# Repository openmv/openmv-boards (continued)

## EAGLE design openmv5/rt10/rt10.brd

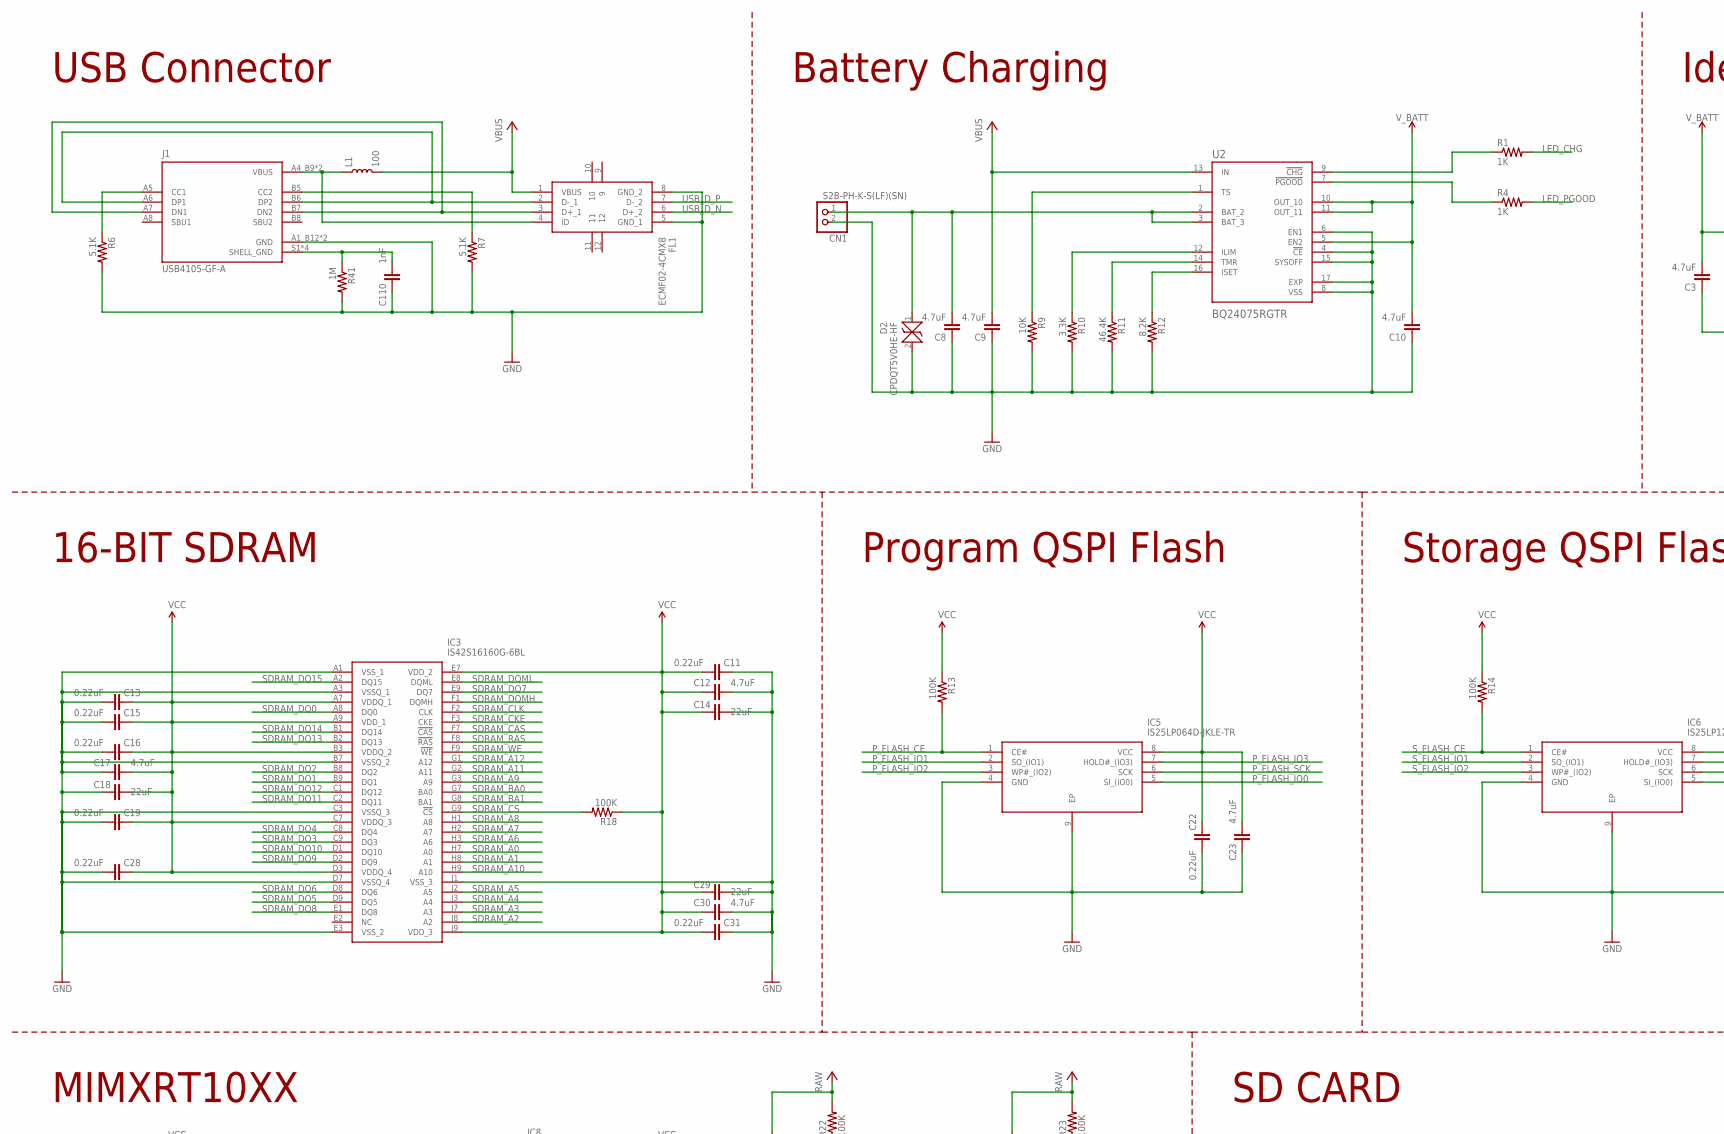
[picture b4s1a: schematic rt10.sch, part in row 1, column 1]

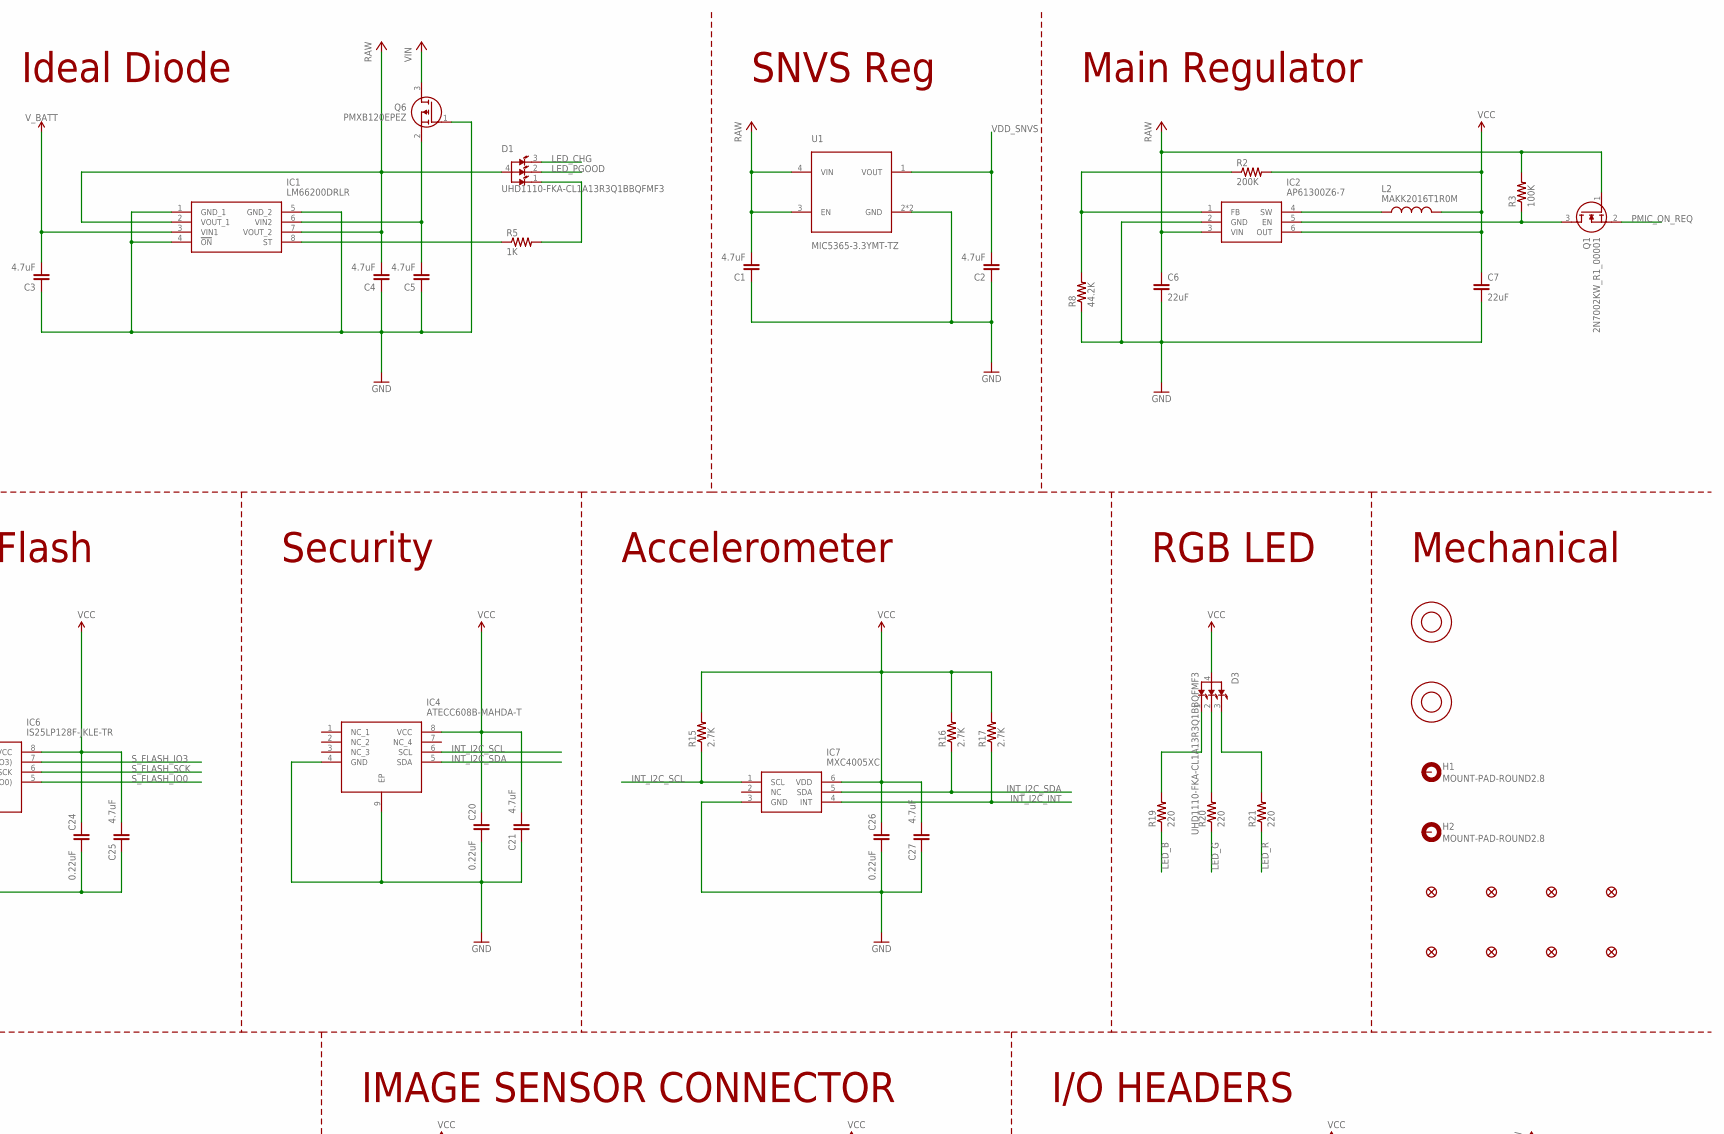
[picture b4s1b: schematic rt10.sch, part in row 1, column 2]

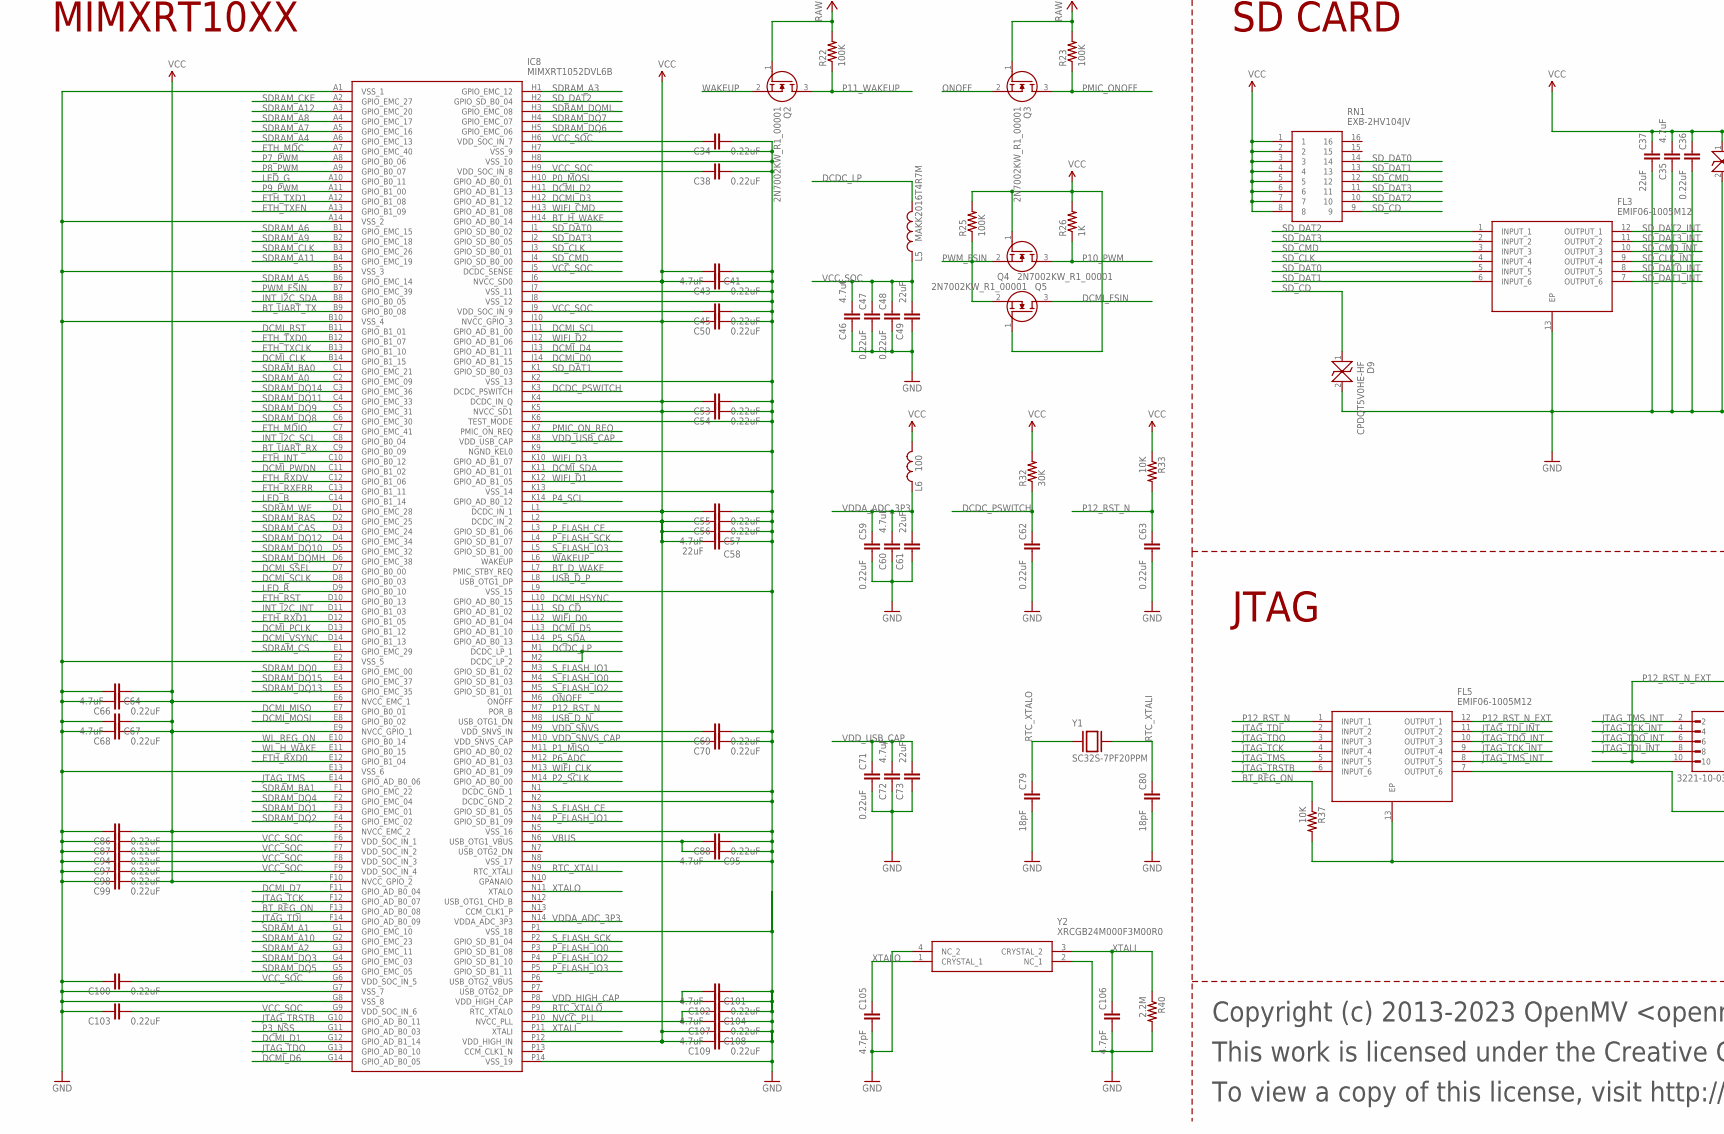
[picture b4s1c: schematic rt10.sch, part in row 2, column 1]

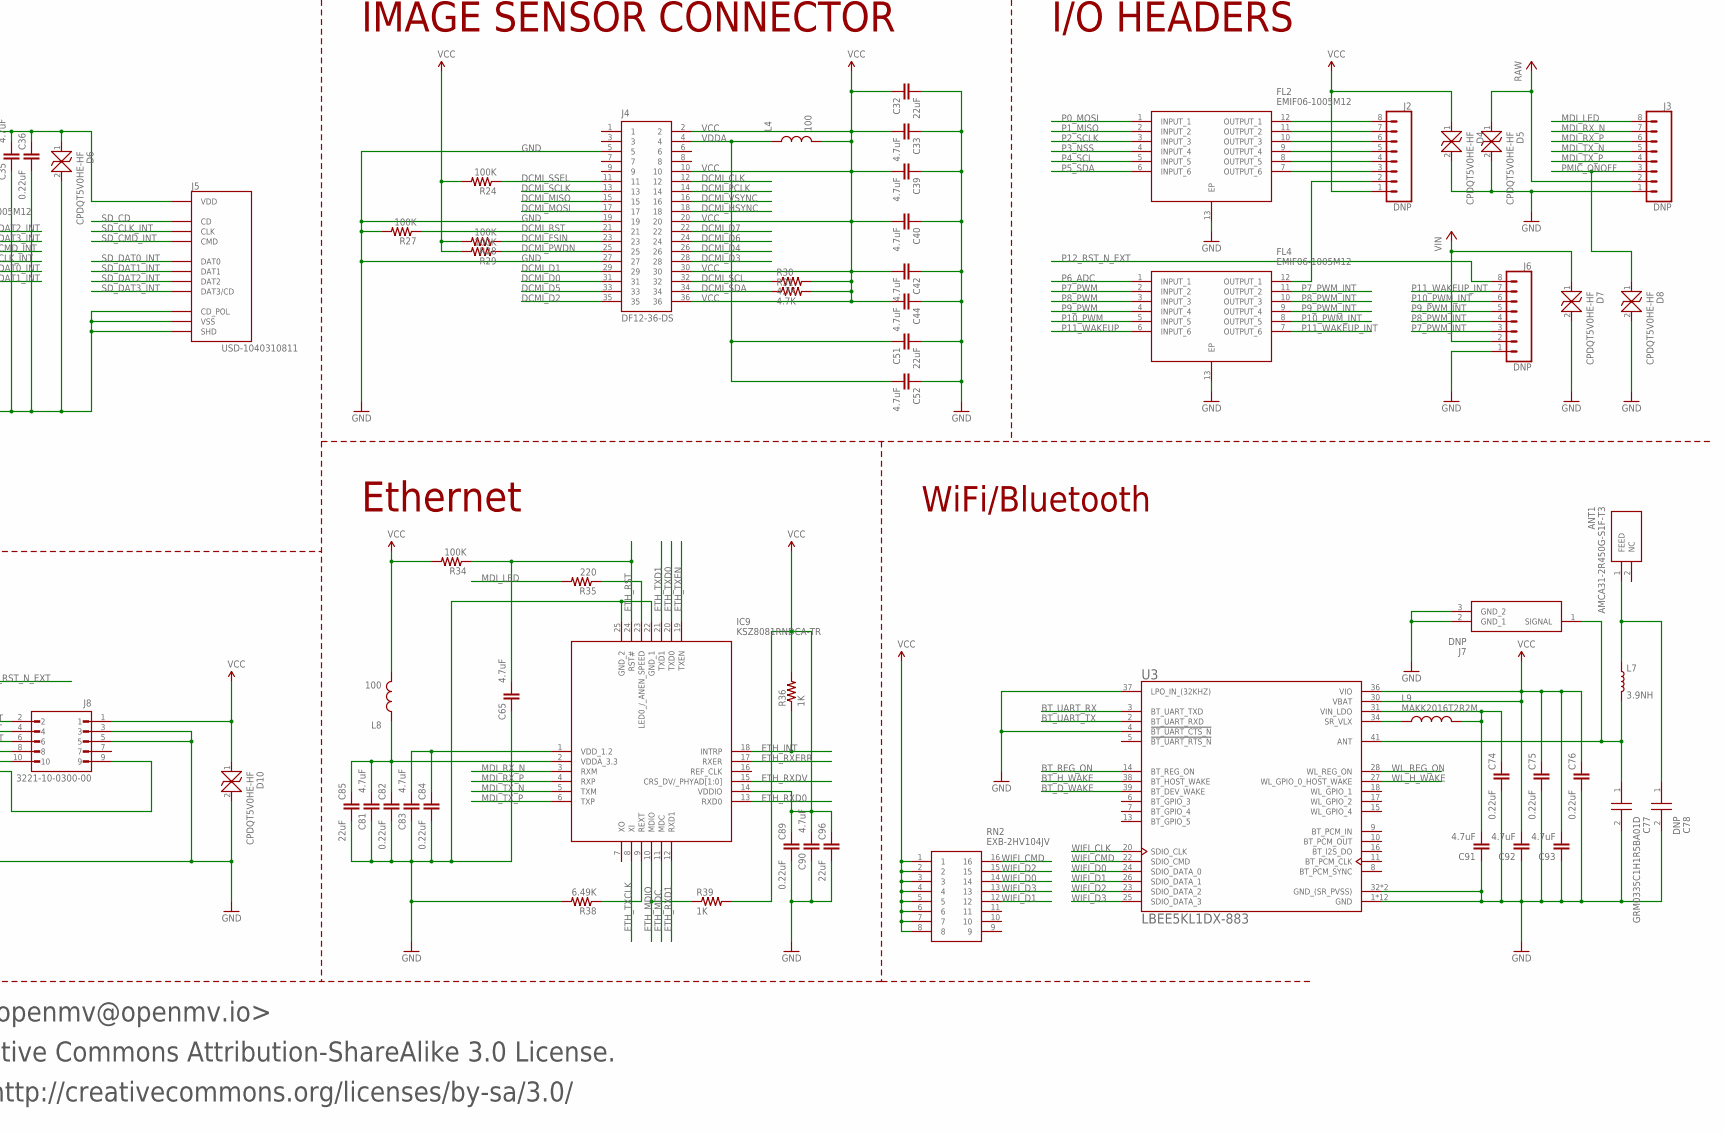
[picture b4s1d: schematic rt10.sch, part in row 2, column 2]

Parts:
ANT1: AMCA31-2R450G-S1F-T3; ANTC3216X140N; MPN AMCA31-2R450G-S1F-T3
C1, C2, C3, C4, C5, C8, C9, C10, C12, C17, C21, C23, C25, C27, C30, C33, C35, C39, C40, C41, C42, C44, C46, C52, C57, C60, C64, C65, C67, C72, C81, C83, C90, C91, C92, C93, C95, C101, C104, C108: 4.7uF; 0402-CAP; MPN JMK105BBJ475MV-F
C6, C7, C14, C18, C29, C32, C37, C49, C51, C58, C61, C73, C85, C96: 22uF; 0805; MPN CL21A226MQQNNNE
C11, C13, C15, C16, C19, C20, C22, C24, C26, C28, C31, C34, C36, C38, C43, C45, C47, C48, C50, C53, C54, C55, C56, C59, C62, C63, C66, C68, C69, C70, C71, C74, C75, C76, C82, C84, C86, C87, C88, C89, C94, C97, C98, C99, C100, C102, C103, C107, C109: 0.22uF; C0201; MPN GRM033R60J224ME15D
C77: GRM0335C1H1R5BA01D; CAPC0603X33N; MPN GRM0335C1H1R5BA01D
C78: DNP; CAPC0603X33N; MPN GRM0335C1H1R5BA01D
C79, C80: 18pF; C0201; MPN GRM0335C1E180JA01D
C105, C106: 4.7pF; C0201; MPN GRM0335C1E4R7CA01D
C110: 1nF; 0402-CAP; MPN VJ0402Y102JXACW1BC
CN1: S2B-PH-K-S(LF)(SN); JST-PH-2-THM-RA; MPN S2B-PH-K-S(LF)(SN)
D1, D3: UHD1110-FKA-CL1A13R3Q1BBQFMF3; LED_UHD1110-FKA-CL1A13R3Q1BBQFMF3; MPN UHD1110-FKA-CL1A13r3q1BBQFMF3
D2, D4, D5, D6, D7, D8, D9, D10: CPDQT5V0HE-HF; CPDQT5V0HEHF; MPN CPDQT5V0HE-HF
FD1, FD2, FD3, FD4, FD5, FD6, FD7, FD8: FIDUCIAL1X2; FIDUCIAL-1X2
FL1: ECMF02-4CMX8; ECMF024CMX8; MPN ECMF02-4CMX8
FL2, FL3, FL4, FL5: EMIF06-1005M12; SON40P150X250X65-13N; MPN EMIF06-1005M12
H1, H2: MOUNT-PAD-ROUND2.8; 2,8-PAD
IC1: LM66200DRLR; SOTFL50P160X60-8N; MPN LM66200DRLR
IC2: AP61300Z6-7; SOTFL50P162X60-6N; MPN AP61300Z6-7
IC3: IS42S16160G-6BL; BGA54C80P9X9_800X800X120; MPN IS42S16160G-6BL
IC4: ATECC608B-MAHDA-T; SON50P300X200X60-9N; MPN ATECC608B-MAHDA-T
IC5: IS25LP064D-JKLE-TR; SON127P500X595X80-9N; MPN IS25LP064D-JKLE-TR
IC6: IS25LP128F-JKLE-TR; SON127P500X595X80-9N; MPN IS25LP128F-JKLE-TR
IC7: MXC4005XC; MPN MXC4005XC
IC8: MIMXRT1052DVL6B; BGA196C65P14X14_1000X1000X143; MPN MIMXRT1052DVL6B
IC9: KSZ8081RNDCA-TR; QFN50P400X400X90-25N; MPN KSZ8081RNDCA-TR
J1: USB4105-GF-A; GCT_USB4105-GF-A; MPN USB4105-GF-A
J2, J3, J6: DNP; 1X08
J4: DF12-36-DS; MPN DF12NB-36DS-0.5V(51)
J5: USD-1040310811; 1040310811; MPN 104031-0811
J7: DNP; 23370191; MPN 2337019-1
J8: 3221-10-0300-00; CNC_3221-10-0300-00; MPN 3221-10-0300-00
L1: 100; 0603; MPN MFBM1V1608-101-R
L2: MAKK2016T1R0M; INDC2016X100N; MPN MAKK2016T1R0M
L4, L6, L8: 100; C0402; MPN MFBM1V1005-101-R
L5: MAKK2016T4R7M; INDC2016X100N; MPN MAKK2016T4R7M
L7: 3.9NH; 0402; MPN L-07C3N9SV6T
L9: MAKK2016T2R2M; INDC2016X100N; MPN MAKK2016T2R2M
M1, M2: 9774030151R; MPN 9774030151R
Q1, Q2, Q3, Q4, Q5: 2N7002KW_R1_00001; SOT65P210X110-3N; MPN 2N7002KW_R1_00001
Q6: PMXB120EPEZ; MPN PMXB120EPEZ
R1, R4, R5, R26, R36, R39: 1K; 0402-RES; MPN CRCW04021K00FKEDC
R2: 200K; 0402-RES; MPN CRCW0402200KFKEDC
R3, R13, R14, R18, R22, R23, R24, R25, R27, R28, R29, R34: 100K; 0402-RES; MPN AC0402FR-07100KL
R6, R7: 5.1K; 0402-RES; MPN RC0402JR-075K1L
R8: 44.2K; 0402-RES; MPN AC0402FR-0744K2L
R9, R33, R37: 10K; 0402-RES; MPN AC0402FR-1310KL
R10: 3.3K; 0402-RES; MPN CRCW04023K30FKEDC
R11: 46.4K; 0402-RES; MPN WR04X4642FTL
R12: 8.2K; 0402-RES; MPN RC0402JR-078K2L
R15, R16, R17: 2.7K; 0402-RES; MPN AC0402JR-072K7L
R19, R20, R21, R35: 220; 0402-RES; MPN CRGCQ0402F220R
R30, R31: 4.7K; 0402-RES; MPN AC0402FR-074K7L
R32: 30K; 0402-RES; MPN 0402WGF3002TCE
R38: 6.49K; 0402-RES; MPN CR0402-FX-6491GLF
R40: 2.2M; 0402-RES; MPN RC0402FR-072M2L
R41: 1M; 0402-RES; MPN CRCW04021M00FKEDC
RN1, RN2: EXB-2HV104JV; EXB2HV104JV
U1: MIC5365-3.3YMT-TZ; VREG_MIC5365-3.3YMT-TZ; MPN MIC5365-3.3YMT-TZ
U2: BQ24075RGTR; QFN50P300X300X100-17N; MPN BQ24075RGTR
U3: LBEE5KL1DX-883; XCVR_LBEE5KL1DX-TEMP; MPN LBEE5KL1DX-883
Y1: SC32S-7PF20PPM; XTAL_ABS07-32.768KHZ-7-T; MPN SC32S-7PF20PPM
Y2: XRCGB24M000F3M00R0; MPN XRCGB24M000F3M00R0

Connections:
ANT: C77.1, J7.1 (SIGNAL), L7.2, U3.41 (ANT)
BAT: C8.2, CN1.1 (2), D2.1, U2.2 (BAT_2), U2.3 (BAT_3)
BT_D_WAKE: IC8.L7 (PMIC_STBY_REQ), U3.39 (BT_DEV_WAKE)
BT_H_WAKE: IC8.H14 (GPIO_AD_B0_14), U3.38 (BT_HOST_WAKE)
BT_REG_ON: IC8.F13 (GPIO_AD_B0_08), R37.1, U3.14 (BT_REG_ON)
BT_UART_RX: IC8.C9 (GPIO_B0_09), U3.3 (BT_UART_TXD)
BT_UART_TX: IC8.B9 (GPIO_B0_08), U3.2 (BT_UART_RXD)
CC1: J1.A5 (CC1), R6.1
CC2: J1.B5 (CC2), R7.1
CHG: R1.1, U2.9 (!CHG)
DCDC_LP: IC8.M1 (DCDC_LP_1), IC8.M2 (DCDC_LP_2), L5.2
DCDC_PSWITCH: C62.1, IC8.K3 (DCDC_PSWITCH), R32.1
DCMI_CLK: IC8.B14 (GPIO_B1_15), J4.12
DCMI_D0: IC8.J14 (GPIO_AD_B1_15), J4.31
DCMI_D1: IC8.G12 (GPIO_AD_B1_14), J4.29
DCMI_D2: IC8.H11 (GPIO_AD_B1_13), J4.35
DCMI_D3: IC8.H12 (GPIO_AD_B1_12), J4.28
DCMI_D4: IC8.J13 (GPIO_AD_B1_11), J4.26
DCMI_D5: IC8.L13 (GPIO_AD_B1_10), J4.33
DCMI_D6: IC8.G14 (GPIO_AD_B0_05), J4.24
DCMI_D7: IC8.F11 (GPIO_AD_B0_04), J4.22
DCMI_FSIN: J4.23, Q5.3 (D), R28.1
DCMI_HSYNC: IC8.L10 (GPIO_AD_B0_15), J4.18
DCMI_MISO: IC8.E7 (GPIO_B0_01), J4.15
DCMI_MOSI: IC8.E8 (GPIO_B0_02), J4.17
DCMI_PCLK: IC8.D13 (GPIO_B1_12), J4.14
DCMI_PWDN: IC8.C11 (GPIO_B1_02), J4.25, R29.1
DCMI_RST: IC8.B11 (GPIO_B1_01), J4.21, R27.1
DCMI_SCL: IC8.J11 (GPIO_AD_B1_00), J4.32, R30.1
DCMI_SCLK: IC8.D8 (GPIO_B0_03), J4.13
DCMI_SDA: IC8.K11 (GPIO_AD_B1_01), J4.34, R31.1
DCMI_SSEL: IC8.D7 (GPIO_B0_00), J4.11, R24.1
DCMI_VSYNC: IC8.D14 (GPIO_B1_13), J4.16
D_N: FL1.3 (D+_1), J1.A7 (DN1), J1.B7 (DN2)
D_P: FL1.2 (D-_1), J1.A6 (DP1), J1.B6 (DP2)
EN: IC2.5 (EN), Q1.3 (D), R3.1
ETH_INT: IC8.C10 (GPIO_B0_12), IC9.18 (INTRP), R36.1
ETH_LED: IC9.23 (LED0_/_ANEN_SPEED), R35.1
ETH_MDC: IC8.A7 (GPIO_EMC_40), IC9.11 (MDC)
ETH_MDIO: IC8.C7 (GPIO_EMC_41), IC9.10 (MDIO), R39.1
ETH_RST: C65.2, IC8.D10 (GPIO_B0_13), IC9.24 (RST#), R34.1
ETH_RXD0: IC8.E12 (GPIO_B1_04), IC9.13 (RXD0)
ETH_RXD1: IC8.D12 (GPIO_B1_05), IC9.12 (RXD1)
ETH_RXDV: IC8.C12 (GPIO_B1_06), IC9.15 (CRS_DV/_PHYAD[1:0])
ETH_RXERR: IC8.C13 (GPIO_B1_11), IC9.17 (RXER)
ETH_TXCLK: IC8.B13 (GPIO_B1_10), IC9.8 (XI)
ETH_TXD0: IC8.B12 (GPIO_B1_07), IC9.20 (TXD0)
ETH_TXD1: IC8.A12 (GPIO_B1_08), IC9.21 (TXD1)
ETH_TXEN: IC8.A13 (GPIO_B1_09), IC9.19 (TXEN)
ETH_VDDA_3.3: C81.2, C82.1, C85.1, IC9.2 (VDDA_3.3), L8.1
ETH_VDD_1.2: C83.2, C84.1, IC9.1 (VDD_1.2)
FB: IC2.1 (FB), R2.1, R8.2
FEED: ANT1.1 (FEED), C78.1, L7.1
GND: C1.1, C2.1, C3.1, C4.1, C5.1, C6.2, C7.2, C8.1, C9.1, C10.1, C11.1, C12.2, C13.2, C14.2, C15.2, C16.2, C17.1, C18.1, C19.2, C20.2, C21.1, C22.2, C23.1, C24.2, C25.1, C26.2, C27.1, C28.2, C29.2, C30.2, C31.1, C32.2, C33.1, C34.2, C35.1, C36.2, C37.2, C38.2, C39.1, C40.1, C41.1, C42.1, C43.2, C44.1, C45.2, C46.1, C47.2, C48.2, C49.1, C50.2, C51.2, C52.1, C53.2, C54.2, C55.2, C56.2, C57.1, C58.1, C59.2, C60.1, C61.1, C62.2, C63.2, C64.2, C65.1, C66.1, C67.2, C68.1, C69.2, C70.2, C71.2, C72.1, C73.1, C74.2, C75.2, C76.2, C77.2, C78.2, C79.2, C80.2, C81.1, C82.2, C83.1, C84.2, C85.2, C86.1, C87.1, C88.2, C89.2, C90.1, C91.1, C92.1, C93.1, C94.1, C95.1, C96.2, C97.1, C98.1, C99.1, C100.1, C101.1, C102.2, C103.1, C104.1, C105.2, C106.2, C107.2, C108.1, C109.2, C110.1, CN1.2 (1), D2.2, D4.2, D5.2, D6.2, D7.2, D8.2, D9.2, D10.2, FL1.5 (GND_1), FL1.8 (GND_2), FL2.13 (EP), FL3.13 (EP), FL4.13 (EP), FL5.13 (EP), IC1.1 (GND_1), IC1.4 (!ON), IC1.5 (GND_2), IC2.2 (GND), IC3.A1 (VSS_1), IC3.A3 (VSSQ_1), IC3.B7 (VSSQ_2), IC3.C3 (VSSQ_3), IC3.D7 (VSSQ_4), IC3.E3 (VSS_2), IC3.J1 (VSS_3), IC4.4 (GND), IC4.9 (EP), IC5.4 (GND), IC5.9 (EP), IC6.4 (GND), IC6.9 (EP), IC7.3 (GND), IC8.A1 (VSS_1), IC8.A14 (VSS_2), IC8.B5 (VSS_3), IC8.B10 (VSS_4), IC8.E2 (VSS_5), IC8.E13 (VSS_6), IC8.G7 (VSS_7), IC8.G8 (VSS_8), IC8.H7 (VSS_9), IC8.H8 (VSS_10), IC8.J7 (VSS_11), IC8.J8 (VSS_12), IC8.K2 (VSS_13), IC8.K6 (TEST_MODE), IC8.K9 (NGND_KEL0), IC8.K13 (VSS_14), IC8.L9 (VSS_15), IC8.N1 (DCDC_GND_1), IC8.N2 (DCDC_GND_2), IC8.N5 (VSS_16), IC8.N8 (VSS_17), IC8.P1 (VSS_18), IC8.P14 (VSS_19), IC9.22 (GND_1), IC9.25 (GND_2), J1.A1_B12 (GND), J1.B1_A12 (GND), J3.1, J4.5, J4.19, J4.27, J5.CD$2 (CD_POL), J5.G$1 (SHD), J5.G$2 (SHD), J5.G$3 (SHD), J5.G$4 (SHD), J5.P$6 (VSS), J6.1, J7.2 (GND_1), J7.3 (GND_2), J8.3, J8.5, Q6.1 (G), R6.2, R7.2, R8.1, R9.2, R10.2, R11.2, R12.2, R27.2, R37.2, R38.2, R40.2, R41.2, U1.2 (GND), U1.EP (GND), U2.4 (!CE), U2.6 (EN1), U2.8 (VSS), U2.15 (SYSOFF), U2.17 (EXP), U3.1 (GND), U3.4 (!BT_UART_CTS_N), U3.12 (GND), U3.19 (GND), U3.21 (GND), U3.29 (GND), U3.32 (GND_(SR_PVSS)), U3.33 (GND_(SR_PVSS)), U3.35 (GND), U3.37 (LPO_IN_(32KHZ)), U3.40 (GND), U3.42 (GND), U3.43 (GND), U3.44 (GND), U3.45 (GND), U3.46 (GND), Y2.2 (NC_1), Y2.4 (NC_2)
ILIM: R10.1, U2.12 (ILIM)
INT_I2C_INT: IC7.4 (INT), IC8.D11 (GPIO_B1_03), R17.1
INT_I2C_SCL: IC4.6 (SCL), IC7.1 (SCL), IC8.C8 (GPIO_B0_04), R15.1
INT_I2C_SDA: IC4.5 (SDA), IC7.5 (SDA), IC8.B8 (GPIO_B0_05), R16.1
ISET: R12.1, U2.16 (ISET)
JTAG_TCK: FL5.4 (INPUT_4), IC8.F12 (GPIO_AD_B0_07)
JTAG_TCK_INT: FL5.9 (OUTPUT_4), J8.4
JTAG_TDI: FL5.2 (INPUT_2), IC8.F14 (GPIO_AD_B0_09)
JTAG_TDI_INT: FL5.11 (OUTPUT_2), J8.8
JTAG_TDO: FL5.3 (INPUT_3), IC8.G13 (GPIO_AD_B0_10)
JTAG_TDO_INT: FL5.10 (OUTPUT_3), J8.6
JTAG_TMS: FL5.5 (INPUT_5), IC8.E14 (GPIO_AD_B0_06)
JTAG_TMS_INT: FL5.8 (OUTPUT_5), J8.2
JTAG_TRSTB: FL5.6 (INPUT_6), IC8.G10 (GPIO_AD_B0_11)
JTAG_TRSTB_INT: FL5.7 (OUTPUT_6), J8.9
LED_B: IC8.C14 (GPIO_B1_14), R19.1
LED_B_INT: D3.1 (BLUE), R19.2
LED_CHG: D1.3 (RED), R1.2
LED_G: IC8.A10 (GPIO_B0_11), R20.1
LED_G_INT: D3.2 (GREEN), R20.2
LED_PGOOD: D1.2 (GREEN), R4.2
LED_R: IC8.D9 (GPIO_B0_10), R21.1
LED_R_INT: D3.3 (RED), R21.2
LED_ST: D1.1 (BLUE), R5.2
MDI_LED: J3.8, R35.2
MDI_RX_N: IC9.3 (RXM), J3.7
MDI_RX_P: IC9.4 (RXP), J3.6
MDI_TX_N: IC9.5 (TXM), J3.5
MDI_TX_P: IC9.6 (TXP), J3.4
NVCC_PLL: C104.2, C107.1, IC8.P10 (NVCC_PLL)
ONOFF: IC8.M6 (ONOFF), Q3.2 (S)
P0_MOSI: FL2.1 (INPUT_1), IC8.H10 (GPIO_AD_B0_01)
P0_MOSI_INT: FL2.12 (OUTPUT_1), J2.8
P1_MISO: FL2.2 (INPUT_2), IC8.M11 (GPIO_AD_B0_02)
P1_MISO_INT: FL2.11 (OUTPUT_2), J2.7
P2_SCLK: FL2.3 (INPUT_3), IC8.M14 (GPIO_AD_B0_00)
P2_SCLK_INT: FL2.10 (OUTPUT_3), J2.6
P3_NSS: FL2.4 (INPUT_4), IC8.G11 (GPIO_AD_B0_03)
P3_NSS_INT: FL2.9 (OUTPUT_4), J2.5
P4_SCL: FL2.5 (INPUT_5), IC8.K14 (GPIO_AD_B0_12)
P4_SCL_INT: FL2.8 (OUTPUT_5), J2.4
P5_SDA: FL2.6 (INPUT_6), IC8.L14 (GPIO_AD_B0_13)
P5_SDA_INT: FL2.7 (OUTPUT_6), J2.3
P6_ADC: FL4.1 (INPUT_1), IC8.M12 (GPIO_AD_B1_03)
P6_ADC_INT: FL4.12 (OUTPUT_1), J2.2
P7_PWM: FL4.2 (INPUT_2), IC8.A8 (GPIO_B0_06)
P7_PWM_INT: FL4.11 (OUTPUT_2), J6.3
P8_PWM: FL4.3 (INPUT_3), IC8.A9 (GPIO_B0_07)
P8_PWM_INT: FL4.10 (OUTPUT_3), J6.4
P9_PWM: FL4.4 (INPUT_4), IC8.A11 (GPIO_B1_00)
P9_PWM_INT: FL4.9 (OUTPUT_4), J6.5
P10_PWM: FL4.5 (INPUT_5), Q4.3 (D), R26.1
P10_PWM_INT: FL4.8 (OUTPUT_5), J6.6
P11_WAKEUP: FL4.6 (INPUT_6), Q2.3 (D), R22.1
P11_WAKEUP_INT: FL4.7 (OUTPUT_6), J6.7
P12_RST_N: C63.1, FL5.1 (INPUT_1), IC8.M7 (POR_B), R33.2
P12_RST_N_EXT: FL5.12 (OUTPUT_1), J6.8, J8.10
PGOOD: R4.1, U2.7 (!PGOOD)
PMIC_ONOFF: D8.1, J3.3, Q3.3 (D), R23.1
PMIC_ON_REQ: IC8.K7 (PMIC_ON_REQ), Q1.2 (S)
PWM_FSIN: IC8.B7 (GPIO_EMC_39), Q4.2 (S), Q5.2 (S), R25.1
P_FLASH_CE: IC5.1 (CE#), IC8.L3 (GPIO_SD_B1_06), R13.2
P_FLASH_IO0: IC5.5 (SI_(IO0)), IC8.P3 (GPIO_SD_B1_08)
P_FLASH_IO1: IC5.2 (SO_(IO1)), IC8.N4 (GPIO_SD_B1_09)
P_FLASH_IO2: IC5.3 (WP#_(IO2)), IC8.P4 (GPIO_SD_B1_10)
P_FLASH_IO3: IC5.7 (HOLD#_(IO3)), IC8.P5 (GPIO_SD_B1_11)
P_FLASH_SCK: IC5.6 (SCK), IC8.L4 (GPIO_SD_B1_07)
RAW: C1.2, C4.2, C6.1, D1.4 (ANODE), D5.1, IC1.2 (VOUT_1), IC1.7 (VOUT_2), IC2.3 (VIN), J3.2, Q1.1 (G), Q2.1 (G), Q3.1 (G), R3.2, R22.2, R23.2, U1.3 (EN), U1.4 (VIN)
REXT: IC9.9 (REXT), R38.1
RTC_XTALI: C80.1, IC8.N9 (RTC_XTALI), Y1.2
RTC_XTALO: C79.1, IC8.P9 (RTC_XTALO), Y1.1
SDRAM_A0: IC3.H7 (A0), IC8.C2 (GPIO_EMC_09)
SDRAM_A1: IC3.H8 (A1), IC8.G1 (GPIO_EMC_10)
SDRAM_A2: IC3.J8 (A2), IC8.G3 (GPIO_EMC_11)
SDRAM_A3: IC3.J7 (A3), IC8.H1 (GPIO_EMC_12)
SDRAM_A4: IC3.J3 (A4), IC8.A6 (GPIO_EMC_13)
SDRAM_A5: IC3.J2 (A5), IC8.B6 (GPIO_EMC_14)
SDRAM_A6: IC3.H3 (A6), IC8.B1 (GPIO_EMC_15)
SDRAM_A7: IC3.H2 (A7), IC8.A5 (GPIO_EMC_16)
SDRAM_A8: IC3.H1 (A8), IC8.A4 (GPIO_EMC_17)
SDRAM_A9: IC3.G3 (A9), IC8.B2 (GPIO_EMC_18)
SDRAM_A10: IC3.H9 (A10), IC8.G2 (GPIO_EMC_23)
SDRAM_A11: IC3.G2 (A11), IC8.B4 (GPIO_EMC_19)
SDRAM_A12: IC3.G1 (A12), IC8.A3 (GPIO_EMC_20)
SDRAM_BA0: IC3.G7 (BA0), IC8.C1 (GPIO_EMC_21)
SDRAM_BA1: IC3.G8 (BA1), IC8.F1 (GPIO_EMC_22)
SDRAM_CAS: IC3.F7 (!CAS), IC8.D3 (GPIO_EMC_24)
SDRAM_CKE: IC3.F3 (CKE), IC8.A2 (GPIO_EMC_27)
SDRAM_CLK: IC3.F2 (CLK), IC8.B3 (GPIO_EMC_26)
SDRAM_CS: IC3.G9 (!CS), IC8.E1 (GPIO_EMC_29), R18.2
SDRAM_DQ0: IC3.A8 (DQ0), IC8.E3 (GPIO_EMC_00)
SDRAM_DQ1: IC3.B9 (DQ1), IC8.F3 (GPIO_EMC_01)
SDRAM_DQ2: IC3.B8 (DQ2), IC8.F4 (GPIO_EMC_02)
SDRAM_DQ3: IC3.C9 (DQ3), IC8.G4 (GPIO_EMC_03)
SDRAM_DQ4: IC3.C8 (DQ4), IC8.F2 (GPIO_EMC_04)
SDRAM_DQ5: IC3.D9 (DQ5), IC8.G5 (GPIO_EMC_05)
SDRAM_DQ6: IC3.D8 (DQ6), IC8.H5 (GPIO_EMC_06)
SDRAM_DQ7: IC3.E9 (DQ7), IC8.H4 (GPIO_EMC_07)
SDRAM_DQ8: IC3.E1 (DQ8), IC8.C6 (GPIO_EMC_30)
SDRAM_DQ9: IC3.D2 (DQ9), IC8.C5 (GPIO_EMC_31)
SDRAM_DQ10: IC3.D1 (DQ10), IC8.D5 (GPIO_EMC_32)
SDRAM_DQ11: IC3.C2 (DQ11), IC8.C4 (GPIO_EMC_33)
SDRAM_DQ12: IC3.C1 (DQ12), IC8.D4 (GPIO_EMC_34)
SDRAM_DQ13: IC3.B2 (DQ13), IC8.E5 (GPIO_EMC_35)
SDRAM_DQ14: IC3.B1 (DQ14), IC8.C3 (GPIO_EMC_36)
SDRAM_DQ15: IC3.A2 (DQ15), IC8.E4 (GPIO_EMC_37)
SDRAM_DQMH: IC3.F1 (DQMH), IC8.D6 (GPIO_EMC_38)
SDRAM_DQML: IC3.E8 (DQML), IC8.H3 (GPIO_EMC_08)
SDRAM_RAS: IC3.F8 (!RAS), IC8.D2 (GPIO_EMC_25)
SDRAM_WE: IC3.F9 (!WE), IC8.D1 (GPIO_EMC_28)
SD_CD: D9.1, IC8.L11 (GPIO_AD_B1_02), J5.CD$1 (CD), RN1.9
SD_CLK: FL3.4 (INPUT_4), IC8.J3 (GPIO_SD_B0_01)
SD_CLK_INT: FL3.9 (OUTPUT_4), J5.P$5 (CLK)
SD_CMD: FL3.3 (INPUT_3), IC8.J4 (GPIO_SD_B0_00), RN1.12
SD_CMD_INT: FL3.10 (OUTPUT_3), J5.P$3 (CMD)
SD_DAT0: FL3.5 (INPUT_5), IC8.J1 (GPIO_SD_B0_02), RN1.14
SD_DAT0_INT: FL3.8 (OUTPUT_5), J5.P$7 (DAT0)
SD_DAT1: FL3.6 (INPUT_6), IC8.K1 (GPIO_SD_B0_03), RN1.13
SD_DAT1_INT: FL3.7 (OUTPUT_6), J5.P$8 (DAT1)
SD_DAT2: FL3.1 (INPUT_1), IC8.H2 (GPIO_SD_B0_04), RN1.10
SD_DAT2_INT: FL3.12 (OUTPUT_1), J5.P$1 (DAT2)
SD_DAT3: FL3.2 (INPUT_2), IC8.J2 (GPIO_SD_B0_05), RN1.11
SD_DAT3_INT: FL3.11 (OUTPUT_2), J5.P$2 (DAT3/CD)
SHELL_GND: C110.2, J1.S1 (SHELL_GND), J1.S2 (SHELL_GND), J1.S3 (SHELL_GND), J1.S4 (SHELL_GND), R41.1
SR_VLX: L9.1, U3.34 (SR_VLX)
ST: IC1.8 (ST), R5.1
SW: IC2.4 (SW), L2.1
S_FLASH_CE: IC6.1 (CE#), IC8.N3 (GPIO_SD_B1_05), R14.2
S_FLASH_IO0: IC6.5 (SI_(IO0)), IC8.M4 (GPIO_SD_B1_03)
S_FLASH_IO1: IC6.2 (SO_(IO1)), IC8.M3 (GPIO_SD_B1_02)
S_FLASH_IO2: IC6.3 (WP#_(IO2)), IC8.M5 (GPIO_SD_B1_01)
S_FLASH_IO3: IC6.7 (HOLD#_(IO3)), IC8.L5 (GPIO_SD_B1_00)
S_FLASH_SCK: IC6.6 (SCK), IC8.P2 (GPIO_SD_B1_04)
TMR: R11.1, U2.14 (TMR)
TS: R9.1, U2.1 (TS)
USB_D_N: FL1.6 (D+_2), IC8.M8 (USB_OTG1_DN)
USB_D_P: FL1.7 (D-_2), IC8.L8 (USB_OTG1_DP)
USB_VBUS: FL1.4 (ID), J1.A4_B9 (VBUS), J1.B4_A9 (VBUS), L1.1
VBUS: C9.2, C88.1, C95.2, FL1.1 (VBUS), IC8.N6 (USB_OTG1_VBUS), L1.2, U2.13 (IN)
VCC: C7.1, C11.2, C12.1, C13.1, C14.1, C15.1, C16.1, C17.2, C18.2, C19.1, C20.1, C21.2, C22.1, C23.2, C24.1, C25.2, C26.1, C27.2, C28.1, C29.1, C30.1, C31.2, C32.1, C33.2, C35.2, C36.1, C37.1, C39.2, C40.2, C41.2, C42.2, C43.1, C44.2, C50.1, C53.1, C54.1, C55.1, C56.1, C57.2, C58.2, C64.1, C66.2, C67.1, C68.2, C75.1, C76.1, C86.2, C89.1, C90.2, C92.2, C93.2, C96.1, C99.2, C108.2, C109.1, D3.4 (ANODE), D4.1, D6.1, D10.1, IC2.6 (OUT), IC3.A7 (VDDQ_1), IC3.A9 (VDD_1), IC3.B3 (VDDQ_2), IC3.C7 (VDDQ_3), IC3.D3 (VDDQ_4), IC3.E7 (VDD_2), IC3.J9 (VDD_3), IC4.8 (VCC), IC5.8 (VCC), IC6.8 (VCC), IC7.6 (VDD), IC8.E6 (NVCC_EMC_1), IC8.E9 (NVCC_GPIO_1), IC8.F5 (NVCC_EMC_2), IC8.F10 (NVCC_GPIO_2), IC8.J6 (NVCC_SD0), IC8.J10 (NVCC_GPIO_3), IC8.K4 (DCDC_IN_Q), IC8.K5 (NVCC_SD1), IC8.L1 (DCDC_IN_1), IC8.L2 (DCDC_IN_2), IC8.P12 (VDD_HIGH_IN), IC9.14 (VDDIO), J2.1, J4.2, J4.10, J4.20, J4.30, J4.36, J5.P$4 (VDD), J8.1, L2.2, L4.2, L6.2, L8.2, Q4.1 (G), Q5.1 (G), R2.2, R13.1, R14.1, R15.2, R16.2, R17.2, R18.1, R24.2, R25.2, R26.2, R28.2, R29.2, R30.2, R31.2, R32.2, R33.1, R34.2, R36.2, R39.2, RN1.1, RN1.2, RN1.3, RN1.4, RN1.5, RN1.6, RN1.7, RN1.8, RN2.1, RN2.2, RN2.3, RN2.4, RN2.5, RN2.6, RN2.7, RN2.8, U3.30 (VBAT), U3.36 (VIO)
VCC_SOC: C34.1, C38.1, C45.1, C46.2, C47.1, C48.1, C49.2, C87.2, C94.2, C97.2, C98.2, C100.2, C103.2, IC8.F6 (VDD_SOC_IN_1), IC8.F7 (VDD_SOC_IN_2), IC8.F8 (VDD_SOC_IN_3), IC8.F9 (VDD_SOC_IN_4), IC8.G6 (VDD_SOC_IN_5), IC8.G9 (VDD_SOC_IN_6), IC8.H6 (VDD_SOC_IN_7), IC8.H9 (VDD_SOC_IN_8), IC8.J5 (DCDC_SENSE), IC8.J9 (VDD_SOC_IN_9), L5.1
VDDA: C51.1, C52.2, J4.4, L4.1
VDDA_ADC_3P3: C59.1, C60.2, C61.2, IC8.N14 (VDDA_ADC_3P3), L6.1
VDD_HIGH_CAP: C101.2, C102.1, IC8.P8 (VDD_HIGH_CAP)
VDD_SNVS: C2.2, C69.1, IC8.M9 (VDD_SNVS_IN), U1.1 (VOUT)
VDD_SNVS_CAP: C70.1, IC8.M10 (VDD_SNVS_CAP)
VDD_USB_CAP: C71.1, C72.2, C73.2, IC8.K8 (VDD_USB_CAP)
VIN: D7.1, J6.2, Q6.3 (D)
VIN_INT: C5.2, IC1.6 (VIN2), Q6.2 (S)
VIN_LDO: C74.1, C91.2, L9.2, U3.31 (VIN_LDO)
V_BATT: C3.2, C10.2, IC1.3 (VIN1), U2.5 (EN2), U2.10 (OUT_10), U2.11 (OUT_11)
WAKEUP: IC8.L6 (WAKEUP), Q2.2 (S)
WIFI_CLK: IC8.M13 (GPIO_AD_B1_09), U3.20 (SDIO_CLK)
WIFI_CMD: IC8.H13 (GPIO_AD_B1_08), RN2.16, U3.22 (SDIO_CMD)
WIFI_D0: IC8.L12 (GPIO_AD_B1_04), RN2.14, U3.24 (SDIO_DATA_0)
WIFI_D1: IC8.K12 (GPIO_AD_B1_05), RN2.12, U3.26 (SDIO_DATA_1)
WIFI_D2: IC8.J12 (GPIO_AD_B1_06), RN2.15, U3.23 (SDIO_DATA_2)
WIFI_D3: IC8.K10 (GPIO_AD_B1_07), RN2.13, U3.25 (SDIO_DATA_3)
WL_H_WAKE: IC8.E11 (GPIO_B0_15), U3.27 (WL_GPIO_0_HOST_WAKE)
WL_REG_ON: IC8.E10 (GPIO_B0_14), U3.28 (WL_REG_ON)
XTALI: C106.1, IC8.P11 (XTALI), R40.1, Y2.3 (CRYSTAL_2)
XTALO: C105.1, IC8.N11 (XTALO), Y2.1 (CRYSTAL_1)

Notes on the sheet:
SD CARD
IMAGE SENSOR CONNECTOR
RGB LED
USB Connector
I/O HEADERS
16-BIT SDRAM
WiFi/Bluetooth
Copyright (c) 2013-2023 OpenMV <openmv@openmv.io>
This work is licensed under the Creative Commons Attribution-ShareAlike 3.0 License.
To view a copy of this license, visit http://creativecommons.org/licenses/by-sa/3.0/
Battery Charging
Ideal Diode
SNVS Reg
Main Regulator
Program QSPI Flash
Storage QSPI Flash
Security
Accelerometer
Mechanical
MIMXRT10XX
JTAG
Ethernet

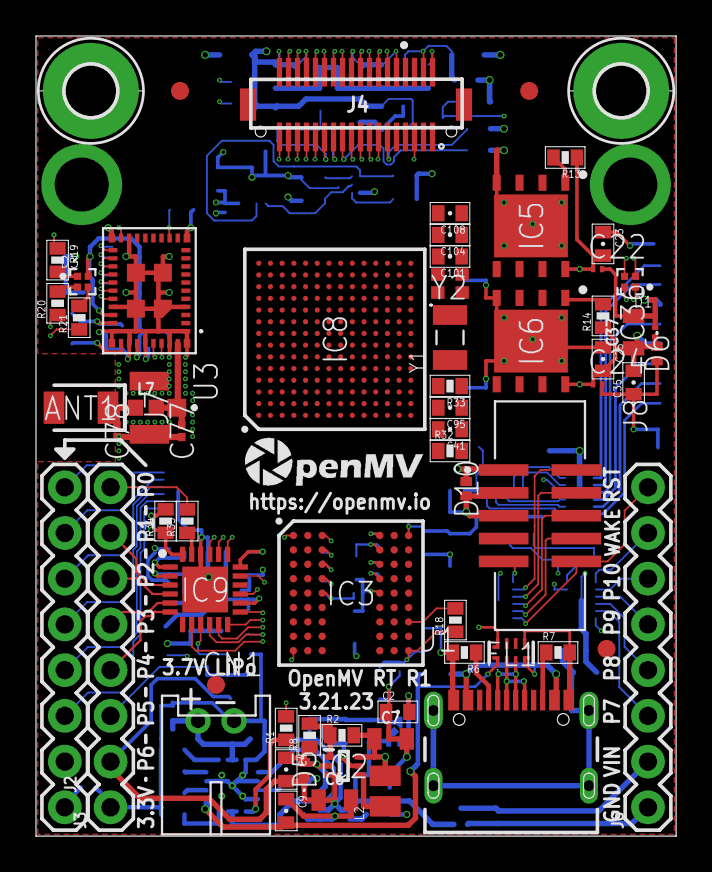
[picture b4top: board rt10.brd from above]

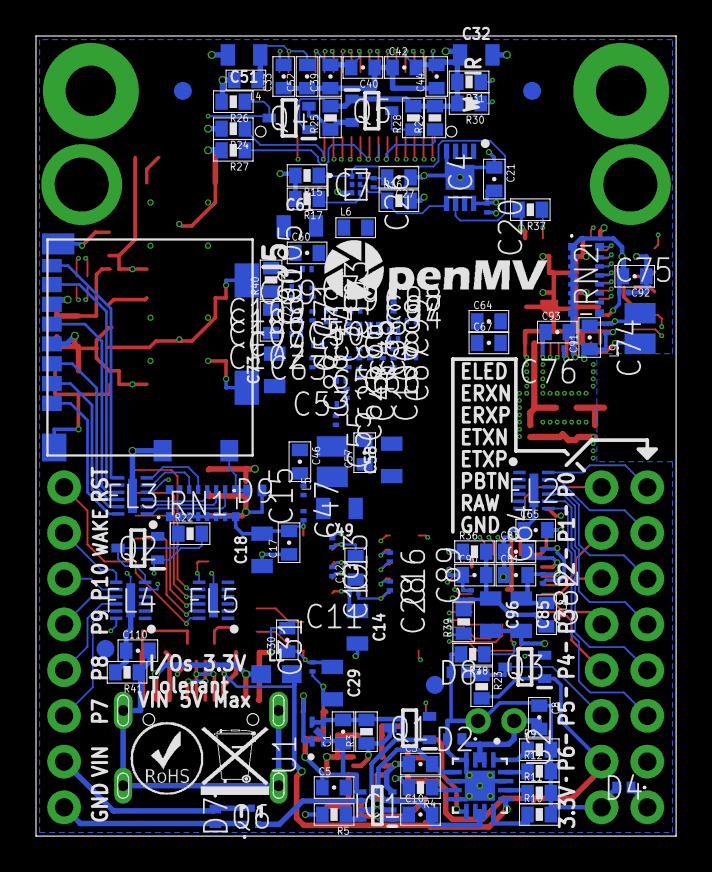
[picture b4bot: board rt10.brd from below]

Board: 8 copper layers, 35.6 x 44.4 mm, 222 parts (153 on the bottom side), 216 nets.

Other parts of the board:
U$1: WEEE
U$2: ROHS
U$3: OMV-LOGO
U$4: OMV-LOGO-SMALL

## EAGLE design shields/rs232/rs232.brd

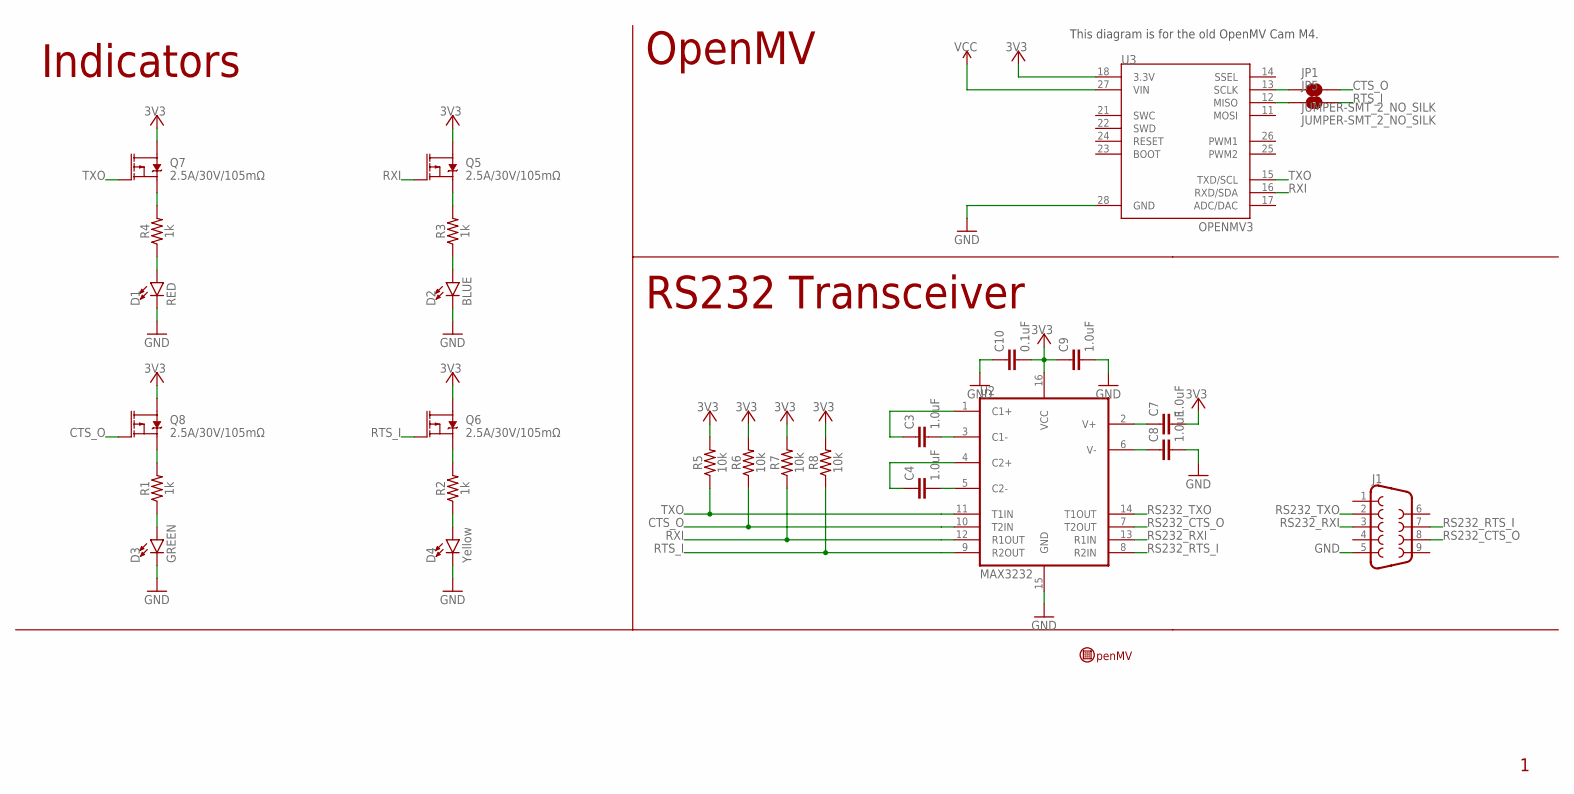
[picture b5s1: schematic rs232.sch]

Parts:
C3, C4, C7, C8, C9: 1.0uF; 0603
C10: 0.1uF; 0603
D1: RED; LED-0603
D2: BLUE; LED-0603
D3: GREEN; LED-0603
D4: Yellow; LED-0603
J1: DB9MALE; DB9_MALE
JP1, JP5: JUMPER-SMT_2_NO_SILK; SMT-JUMPER_2_NO_SILK
Q5, Q6, Q7, Q8: 2.5A/30V/105mΩ; SOT23-3
R1, R2, R3, R4: 1k; 0603
R5, R6, R7, R8: 10k; 0603
U2: MAX3232; SO16
U3: OPENMV3
U$9: OPENMV-LOGO

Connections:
3V3: C7.2, C9.1, C10.2, Q5.3 (D), Q6.3 (D), Q7.3 (D), Q8.3 (D), R5.2, R6.2, R7.2, R8.2, U2.16 (VCC), U3.18 (3.3V)
CTS_O: JP1.2, Q8.1 (G), R6.1, U2.10 (T2IN)
GND: C8.2, C9.2, C10.1, D1.C, D2.C, D3.C, D4.C, J1.5, U2.15 (GND), U3.28 (GND)
INT_CTS_O: JP1.1, U3.13 (SCLK)
INT_RTS_I: JP5.1, U3.12 (MISO)
unnamed: C4.2, U2.5 (C2-)
unnamed: C4.1, U2.4 (C2+)
unnamed: C3.2, U2.3 (C1-)
unnamed: C3.1, U2.1 (C1+)
unnamed: C8.1, U2.6 (V-)
unnamed: Q7.2 (S), R4.2
unnamed: Q5.2 (S), R3.2
unnamed: Q6.2 (S), R2.2
unnamed: C7.1, U2.2 (V+)
unnamed: Q8.2 (S), R1.2
unnamed: D4.A, R2.1
unnamed: D3.A, R1.1
unnamed: D2.A, R3.1
unnamed: D1.A, R4.1
RS232_CTS_O: J1.8, U2.7 (T2OUT)
RS232_RTS_I: J1.7, U2.8 (R2IN)
RS232_RXI: J1.3, U2.13 (R1IN)
RS232_TXO: J1.2, U2.14 (T1OUT)
RTS_I: JP5.2, Q6.1 (G), R8.1, U2.9 (R2OUT)
RXI: Q5.1 (G), R7.1, U2.12 (R1OUT), U3.16 (RXD/SDA)
TXO: Q7.1 (G), R5.1, U2.11 (T1IN), U3.15 (TXD/SCL)
VCC: U3.27 (VIN)

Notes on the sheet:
RS232 Transceiver
OpenMV
This diagram is for the old OpenMV Cam M4.
Indicators

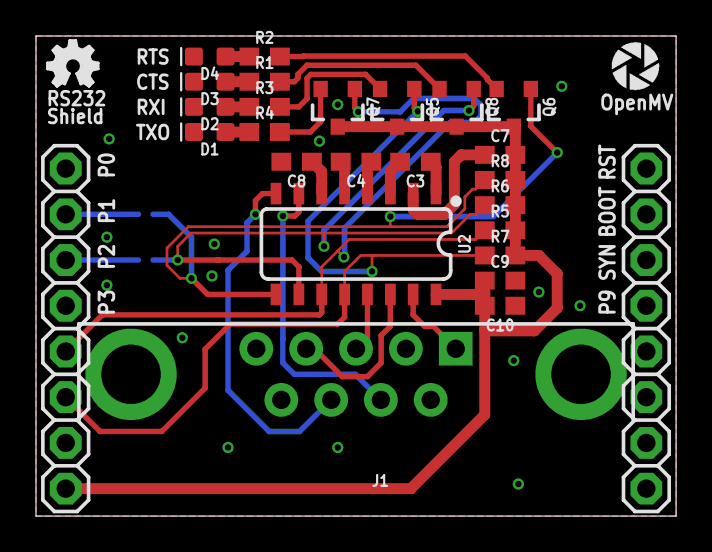
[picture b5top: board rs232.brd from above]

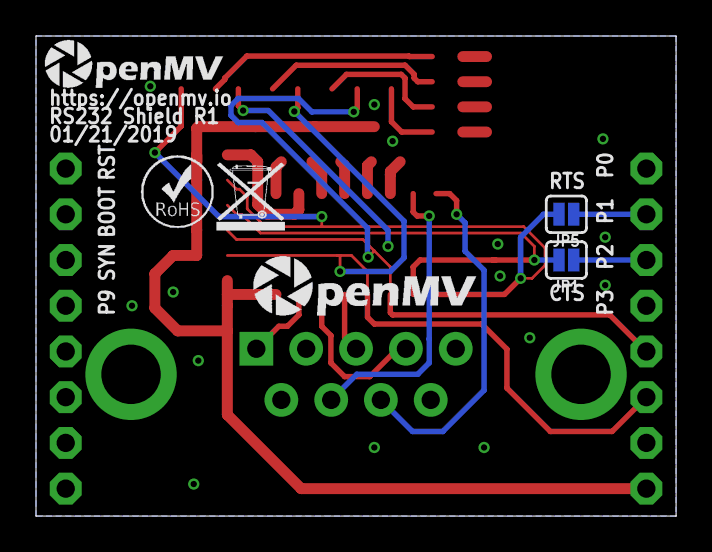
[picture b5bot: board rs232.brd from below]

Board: 2 copper layers, 35.6 x 26.7 mm, 33 parts (6 on the bottom side), 26 nets.

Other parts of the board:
U$3: OMV-LOGO
U$5: ROHS
U$6: WEEE
U$10: OMV-LOGO-SMALL
U$11: OSHW_FILLX100_NOTEXT
